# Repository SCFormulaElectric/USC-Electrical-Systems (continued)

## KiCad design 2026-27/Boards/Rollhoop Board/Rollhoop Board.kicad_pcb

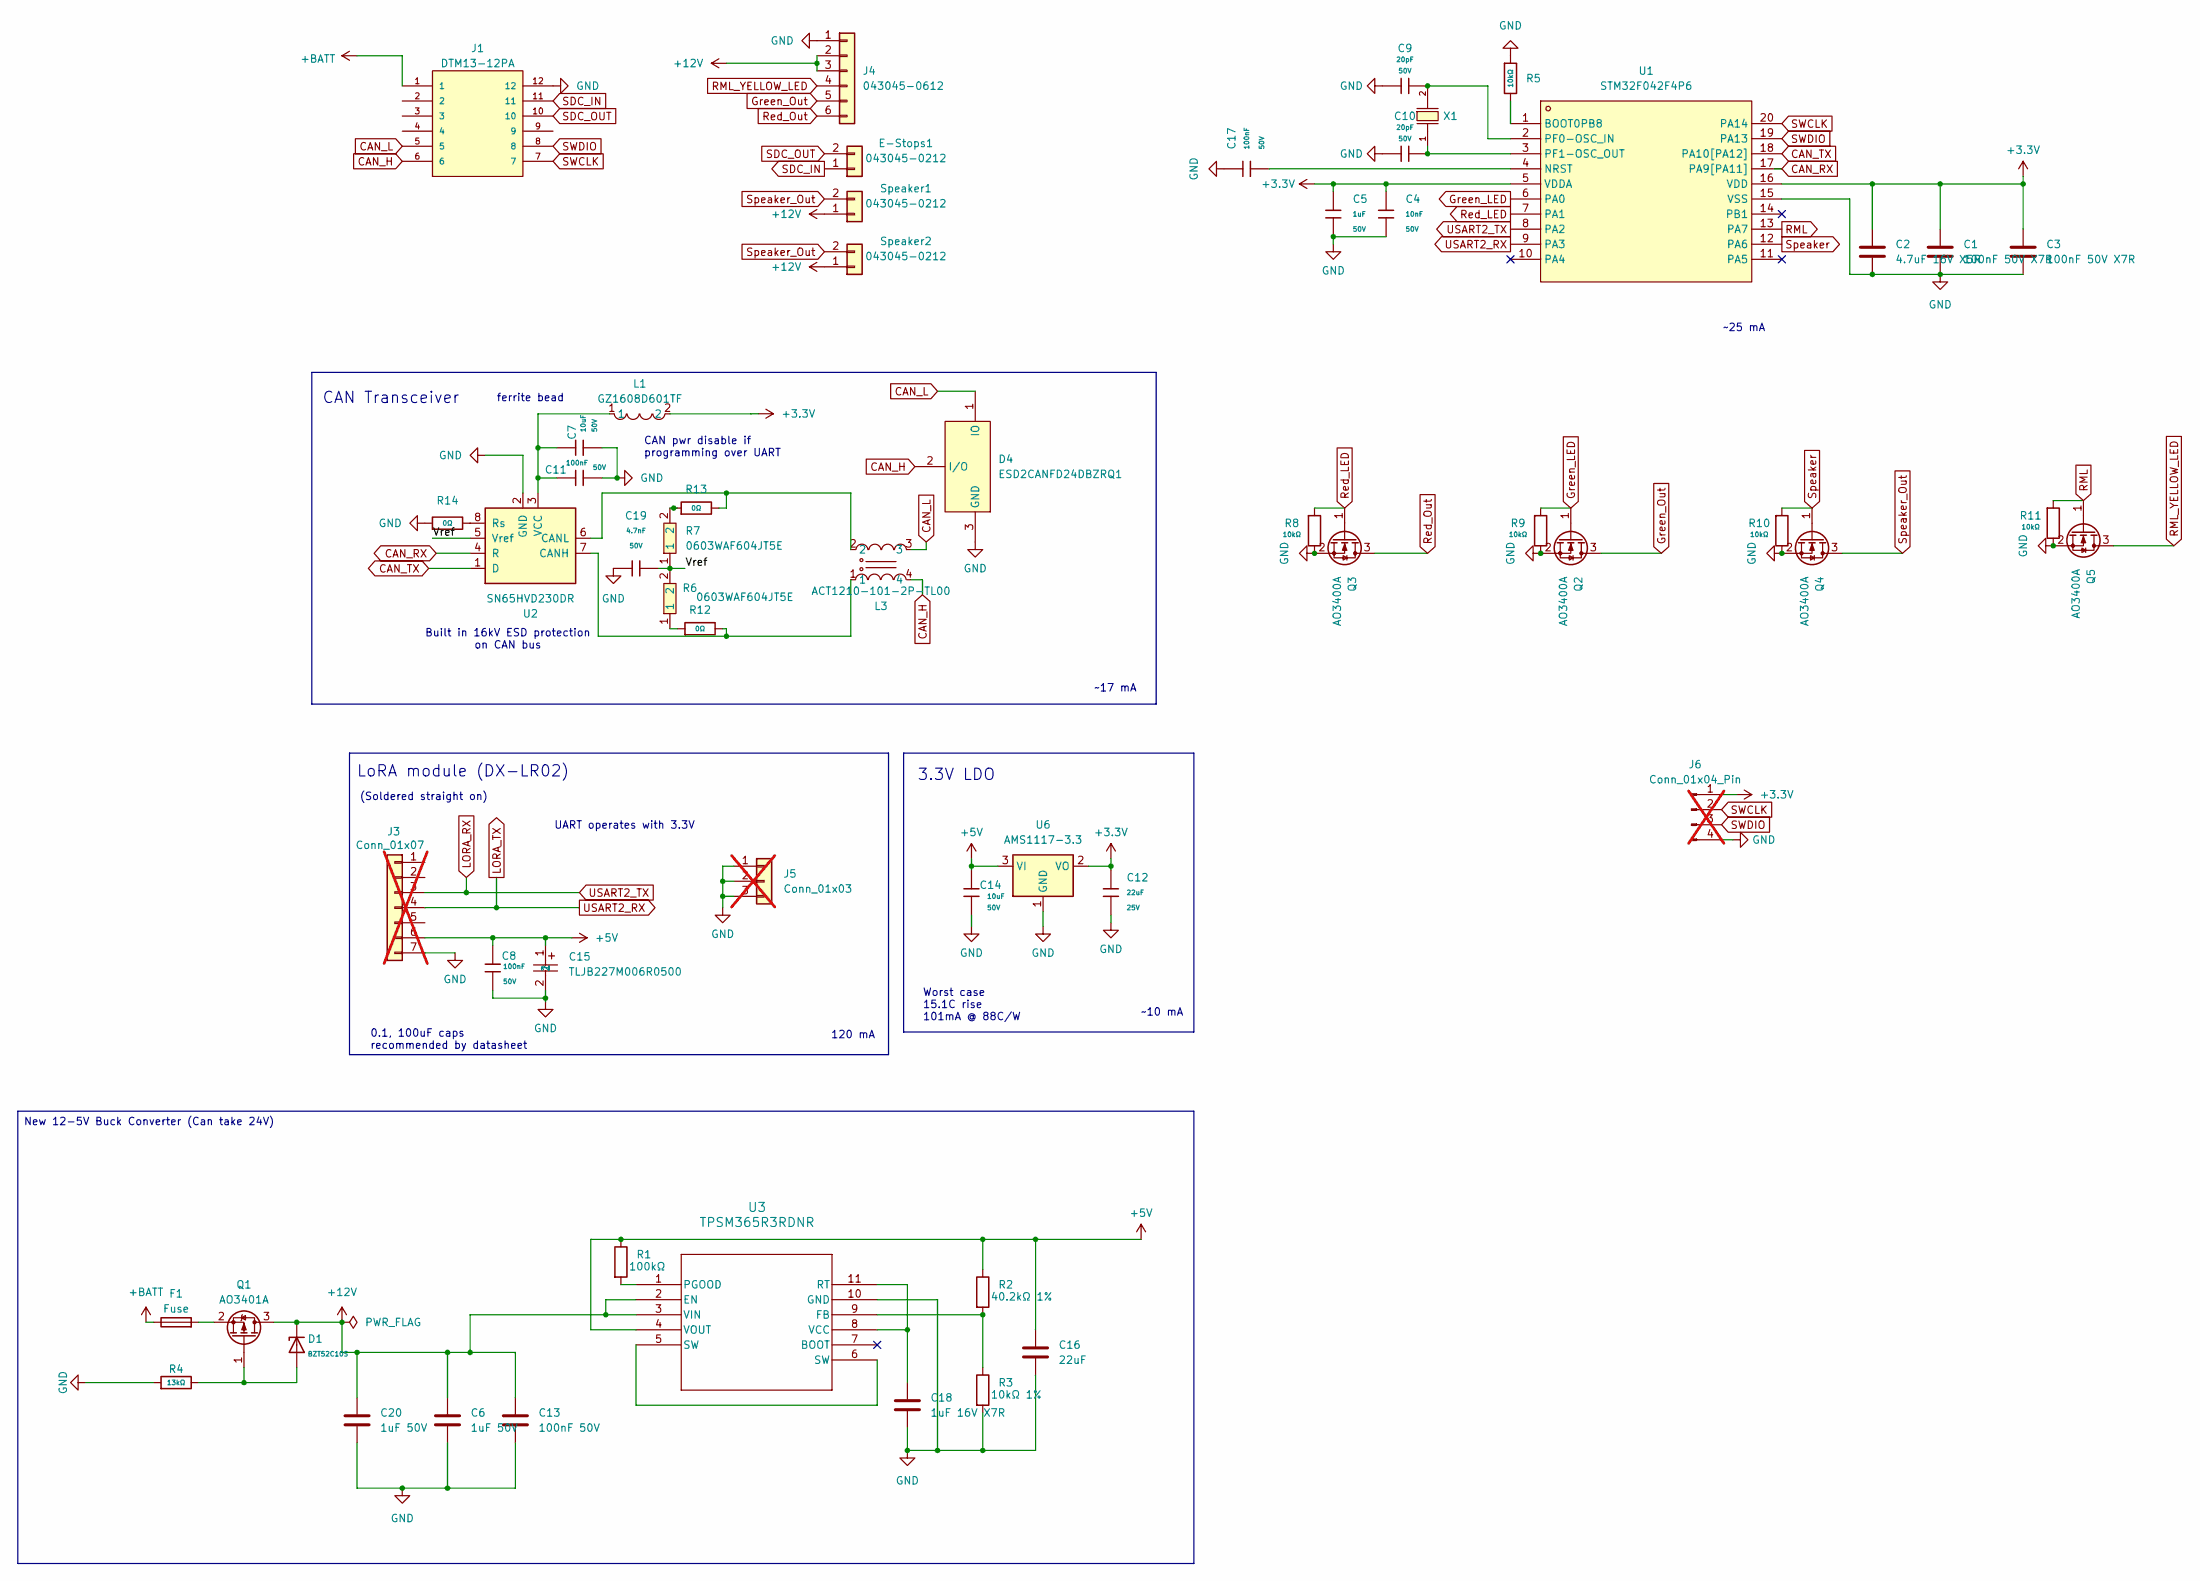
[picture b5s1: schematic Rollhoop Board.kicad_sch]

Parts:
C1, C3: 100nF 50V X7R; C_0603_1608Metric
C2: 4.7uF 16V X5R; C_0805_2012Metric
C4: 10nF; C_0603_1608Metric; Voltage Rated 50V; Tolerance ±10%; Part 0603B103K500NT; LCSC C57112
C5: 1uF; C_0603_1608Metric; Voltage Rated 50V; Tolerance ±10%; Part CL10A105KB8NNNC; LCSC C15849
C6, C20: 1uF 50V; C_1206_3216Metric
C7, C14: 10uF; C_0805_2012Metric; Voltage Rated 50V; Tolerance ±10%; Part GRM21BR61H106KE43L; LCSC C440198
C8, C11, C17: 100nF; C_0603_1608Metric; Voltage Rated 50V; Tolerance ±10%; Part CC0603KRX7R9BB104; LCSC C14663
C9, C10: 20pF; C_0603_1608Metric; Voltage Rated 50V; Tolerance ±5%; Part CL10C200JB8NNNC; LCSC C1648
C12: 22uF; C_1206_3216Metric; Voltage Rated 25V; Tolerance ±10%; Part CL31A226KAHNNNE; LCSC C12891
C13: 100nF 50V; C_0603_1608Metric
C15: TLJB227M006R0500; CP_EIA-3528-21_Kemet-B; LCSC Part C30242
C16: 22uF; C_1210_3225Metric
C18: 1uF 16V X7R; C_0603_1608Metric
C19: 4.7nF; C_0603_1608Metric; Voltage Rated 50V; Tolerance ±10%; Part 0603B472K500NT; LCSC C53987
D1: BZT52C10S; D_SOD-323; Part BZT52C10S; LCSC C19077446
D4: ESD2CANFD24DBZRQ1; SOT-23-3; LCSC Part C20345392
E-Stops1: 043045-0212; Molex_Micro-Fit_3.0_43045-0212_2x01_P3.00mm_Vertical
F1: Fuse; Fuse_1206_3216Metric
J1: DTM13-12PA; DTM1312PA; PARTREV D
J3: Conn_01x07; PinHeader_1x07_P2.54mm_Vertical; not fitted
J4: 043045-0612; Molex_Micro-Fit_3.0_43045-0612_2x03_P3.00mm_Vertical
J5: Conn_01x03; PinHeader_1x03_P2.54mm_Vertical; not fitted
J6: Conn_01x04_Pin; PinHeader_1x04_P2.54mm_Vertical; not fitted
L1: GZ1608D601TF; L_0603_1608Metric; LCSC Part C1002
L3: ACT1210-101-2P-TL00; FILTER-SMD_4P-L3.9-W2.5-BL; LCSC Part C529452
Q1: AO3401A; SOT-23
Q2, Q3, Q4, Q5: AO3400A; SOT-23
R1: 100kΩ; R_0603_1608Metric
R2: 40.2kΩ 1%; R_0603_1608Metric
R3: 10kΩ 1%; R_0603_1608Metric
R4: 13kΩ; R_0603_1608Metric; Overload Voltage (Max) 75V; Tolerance ±1%; Part 0603WAF1302T5E; LCSC C22797
R5, R8, R9, R10, R11: 10kΩ; R_0603_1608Metric; Overload Voltage (Max) 75V; Tolerance ±1%; Part 0603WAF1002T5E; LCSC C25804
R6, R7: 0603WAF604JT5E; R_0603_1608Metric; LCSC Part C23090
R12, R13: 0Ω; R_0402_1005Metric; Overload Voltage (Max) 50V; Tolerance ±1%; Part 0402WGF0000TCE; LCSC C17168
R14: 0Ω; R_0603_1608Metric; Overload Voltage (Max) 75V; Tolerance ±1%; Part 0603WAF0000T5E; LCSC C21189
Speaker1, Speaker2: 043045-0212; Molex_Micro-Fit_3.0_43045-0212_2x01_P3.00mm_Vertical
U1: STM32F042F4P6; TSSOP-20_4.4x6.5mm_P0.65mm; LCSC Part C81002
U2: SN65HVD230DR; SOIC-8_3.9x4.9mm_P1.27mm
U3: TPSM365R3RDNR; QFN-FCMOD_365R6FRDN_TEX
U6: AMS1117-3.3; SOT-223-3_TabPin2
X1: X50328MSB2GI; Crystal_SMD_5032-2Pin_5.0x3.2mm; Frequency Tolerance ±10ppm; Part X50328MSB2GI; LCSC C115962

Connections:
+3.3V: C1.1, C2.1, C3.1, C4.1, C5.1, C12.1, J6.1, L1.2, U1.5 (VDDA), U1.16 (VDD), U6.2 (VO)
+5V: C8.1, C14.1, C15.1, C16.1, J3.6, R1.1, R2.1, U3.4 (VOUT), U6.3 (VI)
+12V: C6.1, C13.1, C20.1, D1.1, J4.2, J4.3, Q1.3 (D), Speaker1.1, Speaker2.1, U3.2 (EN), U3.3 (VIN)
+BATT: F1.1, J1.1
/Vref: C19.1, R6.2, R7.1, U2.5 (Vref)
CAN_H: D4.2 (I/O), J1.6, L3.4
CAN_L: D4.1 (IO), J1.5, L3.3
CAN_RX: U1.17 (PA9[PA11]), U2.4 (R)
CAN_TX: U1.18 (PA10[PA12]), U2.1 (D)
GND: C1.2, C2.2, C3.2, C4.2, C5.2, C6.2, C7.2, C8.2, C9.1, C10.1, C11.2, C12.2, C13.2, C14.2, C15.2, C16.2, C17.1, C18.2, C19.2, C20.2, D4.3 (GND), J1.12, J3.7, J4.1, J5.1, J5.2, J5.3, J6.4, Q2.2 (S), Q3.2 (S), Q4.2 (S), Q5.2 (S), R3.2, R4.1, R5.1, R8.2, R9.2, R10.2, R11.2, R14.1, U1.15 (VSS), U2.2 (GND), U3.10 (GND), U6.1 (GND)
Green_LED: Q2.1 (G), R9.1, U1.6 (PA0)
Green_Out: J4.5, Q2.3 (D)
LORA_RX: J3.3, U1.8 (PA2)
LORA_TX: J3.4, U1.9 (PA3)
unnamed: D1.2, Q1.1 (G), R4.2
unnamed: F1.2, Q1.2 (S)
unnamed: R6.1, R12.1
unnamed: R7.2, R13.1
unnamed: R5.2, U1.1 (BOOT0PB8)
unnamed: C17.2, U1.4 (NRST)
unnamed: C9.2, U1.2 (PF0-OSC_IN), X1.2
unnamed: C10.2, U1.3 (PF1-OSC_OUT), X1.1
unnamed: L3.1, R12.2, U2.7 (CANH)
unnamed: L3.2, R13.2, U2.6 (CANL)
unnamed: R14.2, U2.8 (Rs)
unnamed: C7.1, C11.1, L1.1, U2.3 (VCC)
unnamed: R2.2, R3.1, U3.9 (FB)
unnamed: R1.2, U3.1 (PGOOD)
unnamed: C18.1, U3.8 (VCC), U3.11 (RT)
unnamed: U3.5 (SW), U3.6 (SW)
RML: Q5.1 (G), R11.1, U1.13 (PA7)
RML_YELLOW_LED: J4.4, Q5.3 (D)
Red_LED: Q3.1 (G), R8.1, U1.7 (PA1)
Red_Out: J4.6, Q3.3 (D)
SDC_IN: E-Stops1.1, J1.11
SDC_OUT: E-Stops1.2, J1.10
SWCLK: J1.7, J6.2, U1.20 (PA14)
SWDIO: J1.8, J6.3, U1.19 (PA13)
Speaker: Q4.1 (G), R10.1, U1.12 (PA6)
Speaker_Out: Q4.3 (D), Speaker1.2, Speaker2.2

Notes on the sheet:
CAN pwr disable if programming over UART
(Soldered straight on)
UART operates with 3.3V
~17 mA
3.3V LDO
LoRA module (DX-LR02)
~25 mA
ferrite bead
CAN Transceiver
~10 mA
120 mA
Built in 16kV ESD protection on CAN bus
0.1, 100uF caps recommended by datasheet
Worst case 15.1C rise 101mA @ 88C/W
New 12-5V Buck Converter (Can take 24V)

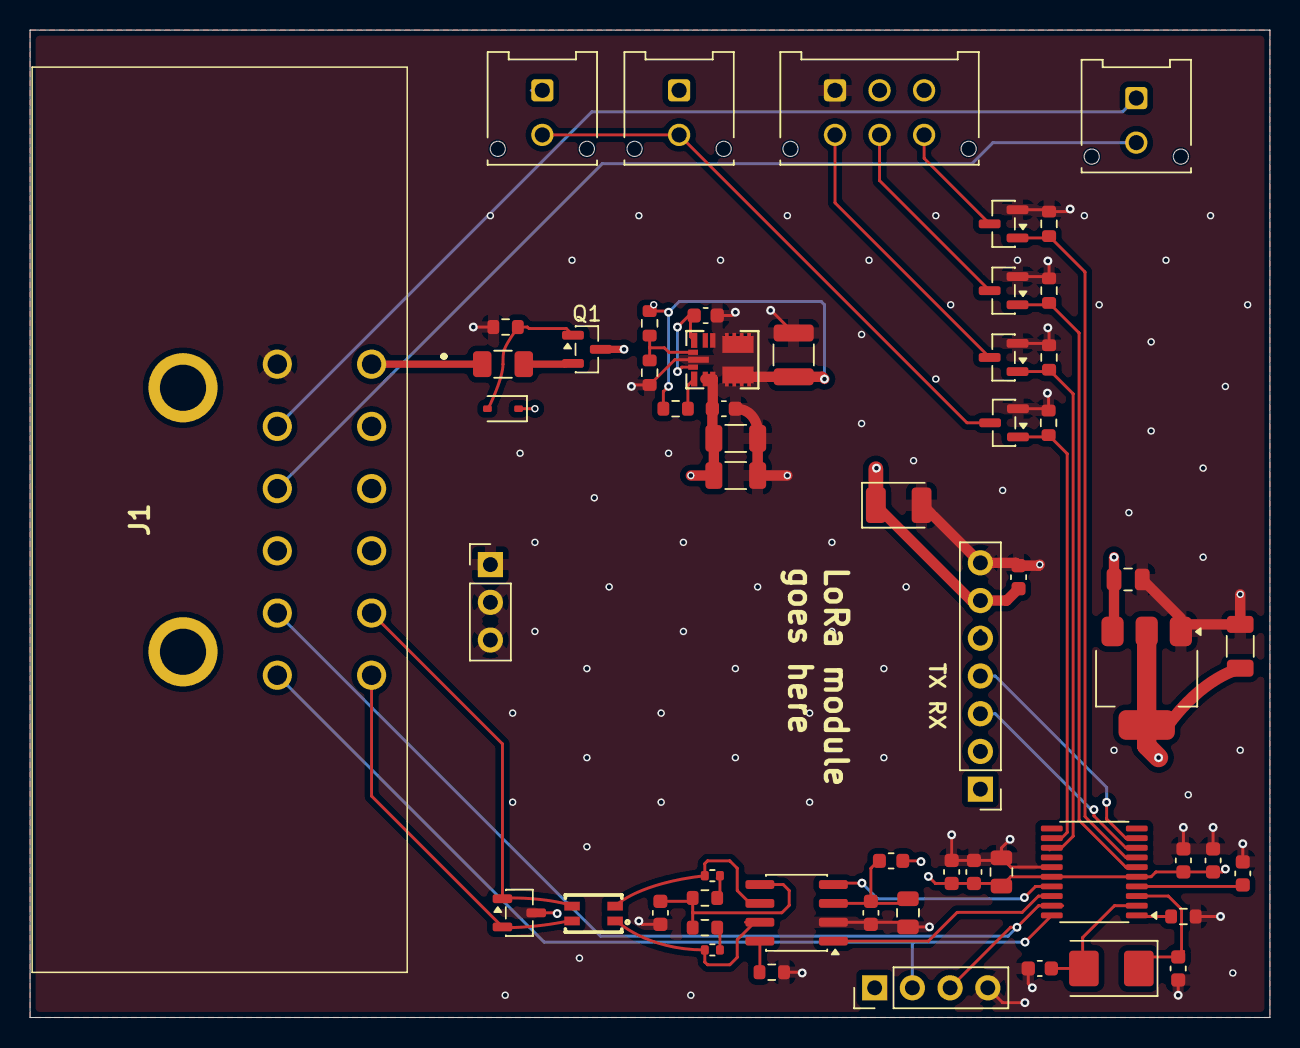
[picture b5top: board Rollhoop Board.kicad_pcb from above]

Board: 4 copper layers, 83.5 x 66.5 mm, 57 parts (0 on the bottom side), 40 nets.

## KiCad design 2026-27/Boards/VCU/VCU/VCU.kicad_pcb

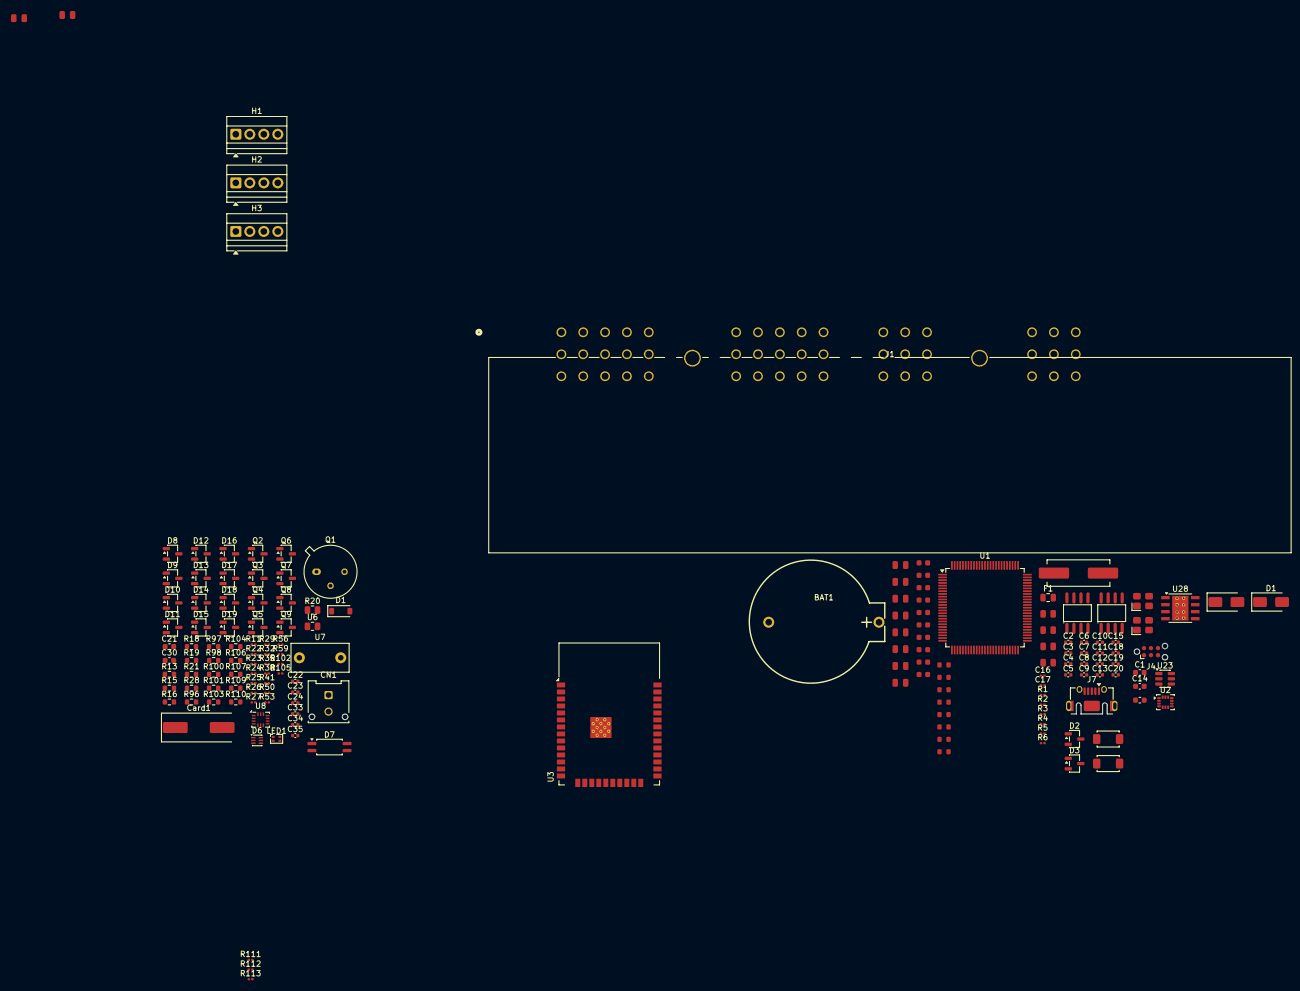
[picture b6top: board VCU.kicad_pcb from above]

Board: 2 copper layers, 161 parts (0 on the bottom side), 104 nets, no tracks yet.

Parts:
BAT1: KH-CR2032-2-1
C1, C14: 30pF; C_0603_1608Metric
C2, C3, C4, C5, C6, C7, C9, C11, C13, C15, C18, C19, C22, C23#2, C24#2, C33, C34, C35: 100nF; C_0402_1005Metric
C8, C10, C12: 1uF; C_0402_1005Metric
C16, C17: 2.2uF; C_0201_0603Metric
C20: 22uF; C_0402_1005Metric
C21, C22#2, C28, C29, C30: 100nF; C_0603
C21#2, C30#2: GRM188Z71C475KE21D; C_0603_1608Metric
C23: 4.7uF; C_0603
C24, C41: 100pF; C_0805
C25, C26: 0603B472K500NT; C_0603
C27, C31#2: CL21A106KAYNNNE; C_0805
C31, C32: 10uF; C_0603
C35#2, C47, C48, C55: 10uF; C_0805
C42: 2.2uF; C_0805
C46: 10nF; C_0805
CN1: 436500200; Molex_Micro-Fit_3.0_43045-0212_2x01_P3.00mm_Vertical
Card1: DM3AT-SF-PEJM5; Crystal_SMD_HC49-SD
D1: SMAJ26CA; D_SMA
D1#2: BZT52C15; D_SOD-123
D2, D3: ESD2CANFD24DBZR; SOT-23-3
D4: SS54; D_SMA
D6: TPD6E004RSER; ST_UQFN-6L_1.5x1.7mm_P0.5mm
D7: SMAJ18A_C148219; SOP-4_4.4x2.6mm_P1.27mm
D8, D9, D10, D11, D12, D13, D14, D15, D16, D17, D18, D19: BAV199_215; SOT-23-3
F1: Fuse; Fuse_0805_2012Metric
H1, H2, H3: PZ254V-11-04P_C2691448; TerminalBlock_Xinya_XY308-2.54-4P_1x04_P2.54mm_Horizontal
J1: 5810148005; CONN48_5810148005_BEL_CIN
J4: TC2030; Tag-Connect_TC2030-IDC-NL_2x03_P1.27mm_Vertical
J7: USB_OTG; USB_Micro-AB_Molex_47590-0001
L1: GZ1608D601TF; L_0603
L4, L5: ACT1210-101-2P-TL00; OSC-SMD_4P-L3.2-W2.5-BL
LED1: KT-0603R; LED_LiteOn_LTST-C295K_1.6x0.8mm
Q1: IRFR9024N_C2874613; TO-5-3
Q2, Q3, Q4, Q5, Q6, Q7, Q8, Q9: AO3400A; SOT-23-3
R1, R2, R3, R4, R5, R6, R11, R22, R23, R24, R25, R26, R27, R29, R32, R35, R38, R41, R50, R53, R56, R59, R102, R105, R111, R112, R113: 10k; R_0201_0603Metric
R7, R8, R9, R10: AC0805FR-0760R4L; R_0805
R13, R16, R19, R97, R101, R103, R106, R109: 0603WAF2200T5E; R_0603_1608Metric
R15, R18, R96, R98: FRC0603F1003TS; R_0603_1608Metric
R20: 0805W8F1000T5E; R_0805_2012Metric
R21, R100, R104, R107, R110: 0603WAF1003T5E; R_0603_1608Metric
R28: 0603WAF1302T5E; R_0603_1608Metric
R51, R52, R54, R55, R67: 47kΩ; R_0603
R53#2: 4.7kΩ; R_0603
R57, R70: 10kΩ; R_0603
S1, S2: Tactile Button, 160gf; SW_TS-1088-AR02016
U1: STM32F405VGTx; LQFP-100_14x14mm_P0.5mm
U2: LSM6DS3; LGA-14_3x2.5mm_P0.5mm_LayoutBorder3x4y
U3: ESP32-WROOM-32E; ESP32-WROOM-32D
U6: FRC0805F8661TS; R_0805_2012Metric
U7: 0154002_DRT; C_Rect_L10.3mm_W5.0mm_P7.50mm_MKS4
U8: LSM6DS3TR-C; Bosch_LGA-14_3x2.5mm_P0.5mm
U23: USBLC6-4SC6; SOT-23-6
U26, U27: SN65HVD230DR; SOIC-8_L4.9-W3.9-P1.27-LS6.0-BL
U28: TPS5430DDA; TI_SO-PowerPAD-8_ThermalVias
X1: X49SM8MSD2SC; CRYSTAL-SMD_L11.5-W4.8-LS12.7

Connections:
5VAIN7: J1.23, J1.28
5VGPIO8: R50.1, U1.59 (PD12)
5VGPIO9: R53.1, U1.60 (PD13)
5VGPIO10: R56.1, U1.61 (PD14)
5VGPIO11: R59.1, U1.62 (PD15)
12VDIN0: J1.6, U1.39 (PE8)
12VDIN1: J1.7, U1.40 (PE9)
12VDIN2: J1.1, U1.41 (PE10)
12VDIN3: J1.2, U1.42 (PE11)
12VDIN4: J1.5, U1.43 (PE12)
12VDIN5: J1.4, U1.44 (PE13)
12VDIN6: J1.3, U1.45 (PE14)
12VDIN7: J1.16, U1.46 (PE15)
+3.3V: C2.2, C3.2, C4.2, C5.1, C6.1, C7.1, C8.1, C19.1, C20.2, C21.2, C22.2, C22#2.2, C23#2.2, C27.2, C28.2, C29.2, C30.1, C30#2.2, C31#2.2, C33.2, C34.2, C35#2.2, C55.1, D8.2, D9.2, D10.2, D11.2, D12.2, D13.2, D14.2, D15.2, D16.2, D17.2, D18.2, D19.2, H2.3, J1.21, J4.2, L1.2, R2.1, R3.2, R5.1, R6.2, R11.2, R22.2, R23.2, R24.2, R25.1, R26.1, R29.2, R32.2, R35.2, R38.2, R41.2, R50.2, R51.2, R52.2, R53.2, R54.2, R55.1, R56.2, R59.2, R67.1, R111.2, R112.2, R113.2, S2.2 (B), U1.11 (VDD), U1.19 (VDD), U1.28 (VDD), U1.50 (VDD), U1.75 (VDD), U1.100 (VDD), U2.5 (VDDIO), U2.8 (VDD), U3.2 (VDD), U8.5 (VDDIO), U8.8 (VDD), U26.3 (VCC), U27.3 (VCC)
+5V: C47.2, R70.1
+12V: C41.1, C48.2, D1#2.1 (K), D7.1, LED1.1 (A), Q1.3 (S), R102.2, R105.2, U28.7 (VIN)
/2Vref: C26.2, R9.1, R10.2, U27.5 (VREF)
/4.5V: C21#2.1, C24#2.1
/ESP32-EN: C18.2, J4.1, R2.2, U3.3 (EN)
/ESP32-IO0: J4.6, R3.1, U3.25 (IO0)
/ESP-RXD: J4.5, U3.34 (RXD0/IO3)
/ESP-TXD: J4.3, U3.35 (TXD0/IO1)
/Vref: C25.2, R7.2, R8.1, U26.5 (VREF)
CAN0+: D3.2 (IO), J1.9, L5.4
CAN0-: D3.1 (IO), J1.8, L5.3
CAN1+: D2.2 (IO), J1.10, L4.4
CAN1-: D2.1 (IO), J1.15, L4.3
CANRX1: U1.81 (PD0), U26.4 (R)
CANRX2: U1.91 (PB5), U27.4 (R)
CANTX1: U1.82 (PD1), U26.1 (D)
CANTX2: U1.92 (PB6), U27.1 (D)
DOUT0: J1.44, Q2.3 (D)
DOUT1: J1.45, Q3.3 (D)
DOUT2: J1.31, Q4.3 (D)
DOUT3: J1.32, Q5.3 (D)
DOUT4: J1.33, Q6.3 (D), R102.1
DOUT5: J1.40, Q7.3 (D), R105.1
DOUT6: J1.41, Q8.3 (D)
DOUT7: J1.42, Q9.3 (D)
EX 12V: CN1.2, F1.2, J1.48, U7.1
GND: BAT1.2, C1.2, C2.1, C3.1, C4.1, C5.2, C6.2, C7.2, C8.2, C9.2, C10.2, C11.2, C12.1, C13.1, C14.1, C15.1, C16.2, C17.2, C18.1, C19.2, C20.1, C21.1, C21#2.2, C22.1, C22#2.1, C23.1, C23#2.1, C24.2, C24#2.2, C25.1, C26.1, C27.1, C28.1, C29.1, C30.2, C30#2.1, C31.2, C31#2.1, C32.2, C33.1, C34.1, C35.2, C35#2.1, C41.2, C47.1, C48.1, C55.2, CN1.1, D1.1 (A1), D2.3 (GND), D3.3 (GND), D4.2, D6.4 (GND), D7.2, D8.1, D9.1, D10.1, D11.1, D12.1, D13.1, D14.1, D15.1, D16.1, D17.1, D18.1, D19.1, H2.4, H3.4, J1.17, J1.18, J1.22, J1.39, J1.46, J1.47, J4.4, J7.5 (GND), Q2.2 (S), Q3.2 (S), Q4.2 (S), Q5.2 (S), R1.2, R4.1, R15.1, R18.1, R21.2, R27.1, R28.1, R57.2, R96.1, R98.1, R100.1, R104.1, R107.1, R110.1, S1.2 (B), U1.10 (VSS), U1.20 (VSSA), U1.27 (VSS), U1.74 (VSS), U1.99 (VSS), U2.6 (GND), U2.7 (GND), U3.1 (GND), U3.15 (GND), U3.38 (GND), U3.39 (GND), U8.2 (SDx), U8.3 (SCx), U8.6 (GND), U8.7 (GND), U23.2 (GND), U26.2 (GND), U26.8 (RS), U27.2 (GND), U27.8 (RS), U28.6 (GND), U28.9 (GNDPAD)
GPIO_DOUT0: R13.1, U1.97 (PE0)
GPIO_DOUT1: R16.1, U1.98 (PE1)
GPIO_DOUT2: R19.1, U1.1 (PE2)
GPIO_DOUT3: R97.1, U1.2 (PE3)
GPIO_DOUT4: R101.1, U1.3 (PE4)
GPIO_DOUT5: R103.1, U1.4 (PE5)
GPIO_DOUT6: R106.1, U1.5 (PE6)
GPIO_DOUT7: R109.1, U1.38 (PE7)
IMU_SPI_CS: R29.1, U1.51 (PB12), U8.12 (CS)
IMU_SPI_INT_PB1: U1.36 (PB1), U8.4 (INT1)
IMU_SPI_MISO: U1.53 (PB14), U8.1 (SDO/SA0)
IMU_SPI_MOSI: U1.54 (PB15), U8.14 (SDA)
IMU_SPI_SCK: U1.52 (PB13), U8.13 (SCL)
unnamed: C24.1, D1.2 (A2), F1.1
unnamed: D1#2.2 (A), Q1.1 (G), R21.1
unnamed: C23.2, R53#2.1
unnamed: LED1.2 (K), R28.2
unnamed: Q1.2 (D), U7.2
unnamed: Q2.1 (G), R13.2, R15.2
unnamed: Q3.1 (G), R16.2, R18.2
unnamed: Q4.1 (G), R19.2, R96.2
unnamed: Q5.1 (G), R97.2, R98.2
unnamed: Q6.1 (G), R100.2, R101.2
unnamed: Q7.1 (G), R103.2, R104.2
unnamed: Q8.1 (G), R106.2, R107.2
unnamed: Q9.1 (G), R109.2, R110.2
unnamed: R20.1, S1.1 (A)
unnamed: R6.1, U1.37 (PB2)
unnamed: C14.2, U1.12 (PH0), X1.1 (OSC1)
unnamed: C1.1, U1.13 (PH1), X1.2 (OSC2)
unnamed: BAT1.1, C9.1, U1.6 (VBAT)
unnamed: C16.1, U1.49 (VCAP_1)
unnamed: C17.1, U1.73 (VCAP_2)
unnamed: C10.1, C11.1, C12.2, C13.2, L1.1, U1.21 (VREF+), U1.22 (VDDA)
unnamed: R5.2, U3.27 (IO16)
unnamed: L4.1, R8.2, U26.7 (CANH)
unnamed: L4.2, R7.1, U26.6 (CANL)
unnamed: L5.1, R9.2, U27.7 (CANH)
unnamed: L5.2, R10.1, U27.6 (CANL)
unnamed: C46.1, U28.1 (BOOT)
unnamed: C46.2, D4.1, U28.8 (PH)
unnamed: R70.2, U6.1 (1_1), U28.4 (VSENSE)
PA9 (VBUS): C35.1, J7.1 (VBUS), R27.2, R53#2.2, R57.1, U1.68 (PA9), U23.5 (VBUS)
PA11 (D-): J7.2 (D-), U1.70 (PA11), U23.3 (I/O2)
PA12 (D+): J7.3 (D+), U1.71 (PA12), U23.1 (I/O1)
RX-UART-BOOT: U1.47 (PB10), U3.33 (IO21)
SD_CLK: D6.5 (IO4), U1.80 (PC12)
SD_CMD: D6.3 (IO3), R24.1, U1.83 (PD2), U1.87 (PD6)
SD_D0: D6.6 (IO5), R26.2, U1.65 (PC8)
SD_D1: R25.2, U1.66 (PC9)
SD_D2: Card1.1 (DAT2), D6.1 (IO1), R22.1, U1.78 (PC10)
SD_D3: Card1.2 (CD/DAT3), D6.2 (IO2), R23.1, U1.79 (PC11)
STM32_SWCLK: H2.2, U1.76 (PA14)
STM32_SWDIO: H2.1, U1.72 (PA13)
STM-BOOT: R1.1, U1.94 (BOOT0), U3.30 (IO18)
STM-NRST: C15.2, R20.2, U1.14 (NRST), U3.31 (IO19)
TCK: H1.3, U3.16 (IO13)
TDI: H1.2, R4.2, U3.14 (IO12)
TDO: H1.4, U3.23 (IO15)
TMS: H1.1, U3.13 (IO14)
TX-UART-BOOT: U1.48 (PB11), U3.36 (IO22)
UART6_UTIL_RX: H3.2, U1.64 (PC7)
UART6_UTIL_TX: H3.1, U1.63 (PC6)
